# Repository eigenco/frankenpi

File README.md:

# frankenpi

This is an experimental project to connect Raspberry Pi with the help of cheap Cyclone IV FPGA board to 8-bit ISA bus to act as multiple different devices.

What is currently implemented (to some degree), i.e. PC can access through ISA
- Mass storage access from a file on the Raspberry Pi (written sectors are flushed every 2 seconds by default)
- Adlib output to optical SPDIF
- Sound Blaster 8-bit mono with DMA and IRQ (basic functions only), output to optical SPDIF
- Gravis Ultrasound (basic wavetable only), output to optical SPDIF
- Roland MT-32 (UART only), output to optical SPDIF
- USB mouse plugged into the Raspberry Pi will appear as a kind of serial mouse in DOS, custom ctmouse driver is provided (start with /v)
- Boot from custom TVGA9000i VGABIOS, i.e. no other devices are required to be present in the ISA bus besides FrakenPi and VGA-adapter

Youtube links:

https://www.youtube.com/watch?v=1ej76w8sHxY

https://www.youtube.com/watch?v=CkwgHHmKaSI

TESTED and working:
- Wolfenstein 3D (SB & Adlib)
- Second Reality (GUS)
- Scream Tracker 3.21 (SB1 and GUS)
- Skyroads (SB & Adlib)
- Keen 4 (Adlib)
- Monkey Island (Adlib/MT32/Mouse)
- Space Quest 3 (Adlib/Mouse)
- Space Quest 4 (Adlib/MT32/Mouse)
- Lotus 3 (Adlib)
- Lemmings (Adlib/Mouse)
- Eye of the Beholder I & II (Adlib/Mouse)
- Indiana Jones and the Fate of Atlantis (Adlib/MT32/Mouse)

Planned
- General MIDI
- MPU-401 support
- Sound Blaster AWE32 wavetable support
- Standard ATA at ports 1f0h-1f7h
- Compatibility improvements
- Boot ROM in the FPGA so hacked VGABIOS isn't required
- VGA output

Used resources
- Harddisk: ports 170h-171h
- SoundBlaster: ports 22ah-22eh corresponding ot base address of 220h, IRQ 7 and DMA 1
- MT32: 330h-331h
- Gravis Ultrasound: ports 341h-347h corresponding to base address of 240h
- Adlib: ports 388h-389h (standard)
- Mouse: port 3f8h and IRQ 4 (COM1)
- Bootcode for custom int 13h resides in hacked VGABIOS at the end of C0000-C7FFF memory region

Further explanation
- Outgoing port operations are transferred from the FPGA to the Raspberry Pi GPIO using dedicated unidirectional 8-bit data bus
- Incoming data from the Raspberry Pi GPIO (PCM, harddisk, mouse) is transferred using dedicated unidirectional 8-bit data bus
- Raspberry Pi: CPU0 handles hdd flushing and mouse, CPU1 handles GPIO transfers, CPU2 handles Adlib, Gravis Ultrasound and MT32 (software selected)
- Raspberry Pi operates with CPU1-CPU3 in isolated mode, all CPUs run at constant 1 GHz and sched_rt_runtime_us is -1
- Raspberry Pi generates sound data 64 samples at a time (16-bit stereo corresponds to 256 bytes it must transfer every 1.45ms or so)
- SPDIF is running in 24-bit 44100 Hz Stereo
- Hardcoded harddisk type is CHS 256/16/63, i.e. approx. 126MiB

Plan for the next PCB
- ICE40HX8K-CT256 (FPGA) seems to be available at Mouser
- IS61WV102416FBLL-10TLI (2 MByte SRAM) seem to be available at Mouser
- Created KiCAD project (PCB_v2)

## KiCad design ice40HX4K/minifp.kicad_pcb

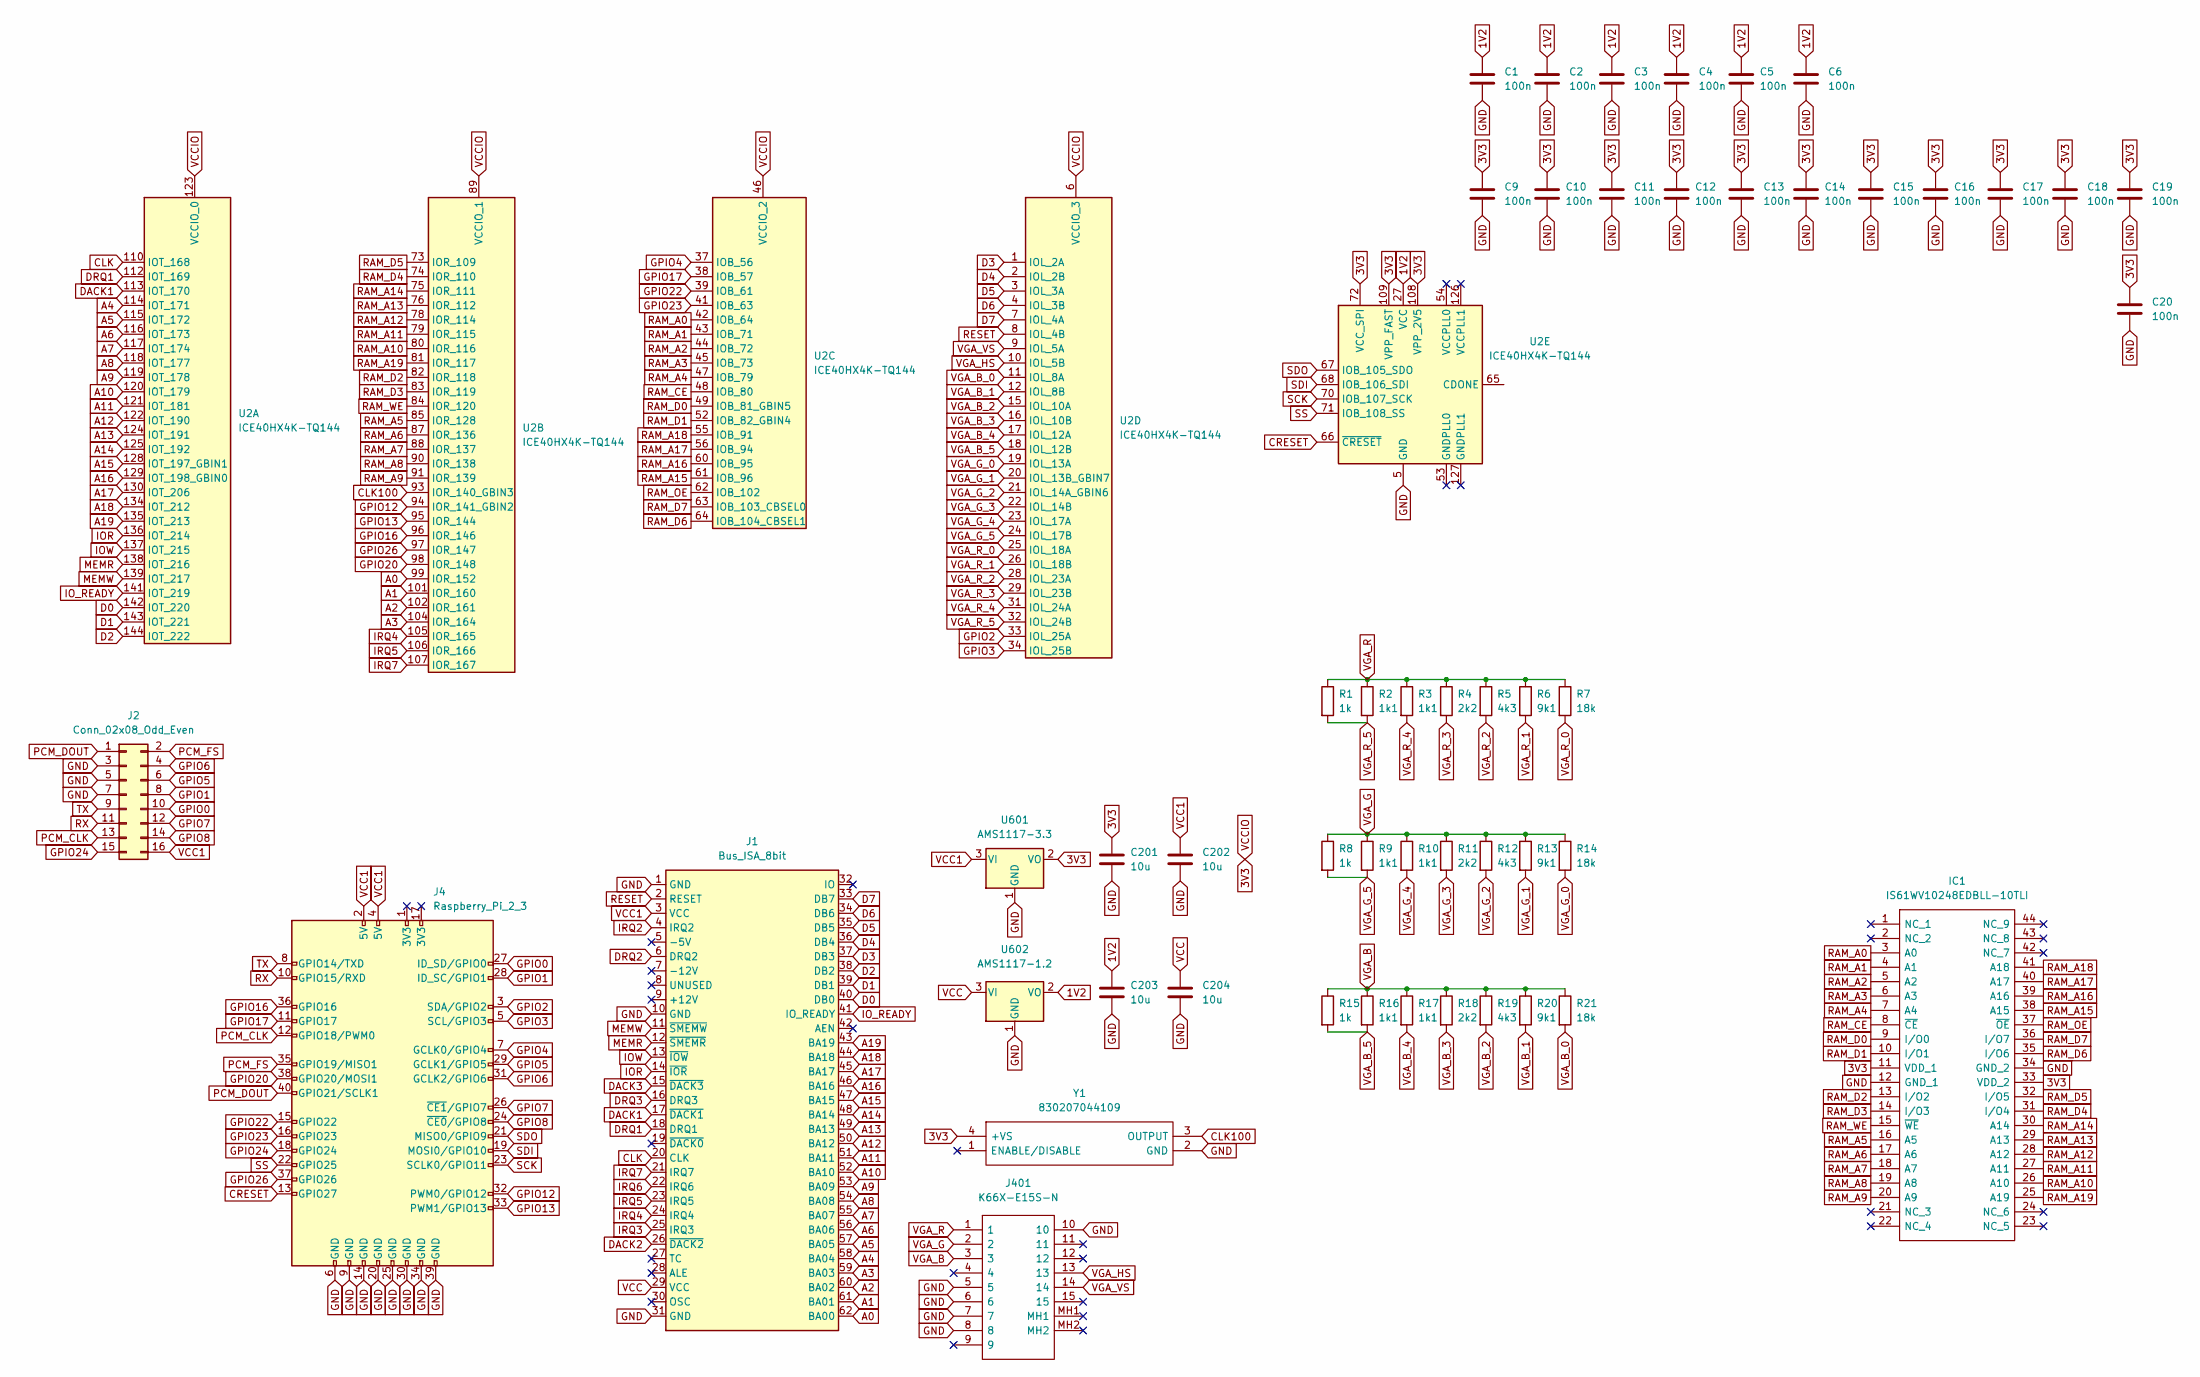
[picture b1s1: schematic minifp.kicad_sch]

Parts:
C1, C2, C3, C4, C5, C6, C9, C10, C11, C12, C13, C14, C15, C16, C17, C18, C19, C20: 100n; C_0603_1608Metric
C201, C202, C203, C204: 10u; C_0603_1608Metric
IC1: IS61WV10248EDBLL-10TLI; SOP80P1176X120-44N; Mouser Part Number 870-61WV10EDBLL10TLI
J1: Bus_ISA_8bit; Conn_Bus_ISA8
J2: Conn_02x08_Odd_Even; PinHeader_2x08_P1.27mm_Vertical
J4: Raspberry_Pi_2_3; PinHeader_2x20_P2.54mm_Vertical
J401: K66X-E15S-N; K66XE15SN; Mouser Part Number 806-K66X-E15S-N
R1, R8, R15: 1k; R_0603_1608Metric
R2, R3, R9, R10, R16, R17: 1k1; R_0603_1608Metric
R4, R11, R18: 2k2; R_0603_1608Metric
R5, R12, R19: 4k3; R_0603_1608Metric
R6, R13, R20: 9k1; R_0603_1608Metric
R7, R14, R21: 18k; R_0603_1608Metric
U2: ICE40HX4K-TQ144; TQFP-144_20x20mm_P0.5mm
U601: AMS1117-3.3; SOT-223-3_TabPin2
U602: AMS1117-1.2; SOT-223-3_TabPin2
Y1: 830207044109; Manufacturer_Part_Number 830207044109

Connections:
1V2: C1.1, C2.1, C3.1, C4.1, C5.1, C6.1, C203.1, U2.27 (VCC), U2.40 (VCC), U2.92 (VCC), U2.111 (VCC), U602.2 (VO)
3V3: C9.1, C10.1, C11.1, C12.1, C13.1, C14.1, C15.1, C16.1, C17.1, C18.1, C19.1, C20.1, C201.1, IC1.11 (VDD_1), IC1.33 (VDD_2), U2.6 (VCCIO_3), U2.30 (VCCIO_3), U2.46 (VCCIO_2), U2.57 (VCCIO_2), U2.72 (VCC_SPI), U2.89 (VCCIO_1), U2.100 (VCCIO_1), U2.108 (VPP_2V5), U2.109 (VPP_FAST), U2.123 (VCCIO_0), U2.131 (VCCIO_0), U601.2 (VO), Y1.4 (+VS)
A0: J1.62 (BA00), U2.99 (IOR_152)
A1: J1.61 (BA01), U2.101 (IOR_160)
A2: J1.60 (BA02), U2.102 (IOR_161)
A3: J1.59 (BA03), U2.104 (IOR_164)
A4: J1.58 (BA04), U2.114 (IOT_171)
A5: J1.57 (BA05), U2.115 (IOT_172)
A6: J1.56 (BA06), U2.116 (IOT_173)
A7: J1.55 (BA07), U2.117 (IOT_174)
A8: J1.54 (BA08), U2.118 (IOT_177)
A9: J1.53 (BA09), U2.119 (IOT_178)
A10: J1.52 (BA10), U2.120 (IOT_179)
A11: J1.51 (BA11), U2.121 (IOT_181)
A12: J1.50 (BA12), U2.122 (IOT_190)
A13: J1.49 (BA13), U2.124 (IOT_191)
A14: J1.48 (BA14), U2.125 (IOT_192)
A15: J1.47 (BA15), U2.128 (IOT_197_GBIN1)
A16: J1.46 (BA16), U2.129 (IOT_198_GBIN0)
A17: J1.45 (BA17), U2.130 (IOT_206)
A18: J1.44 (BA18), U2.134 (IOT_212)
A19: J1.43 (BA19), U2.135 (IOT_213)
CLK: J1.20 (CLK), U2.110 (IOT_168)
CLK100: U2.93 (IOR_140_GBIN3), Y1.3 (OUTPUT)
CRESET: J4.13 (GPIO27), U2.66 (~CRESET)
D0: J1.40 (DB0), U2.142 (IOT_220)
D1: J1.39 (DB1), U2.143 (IOT_221)
D2: J1.38 (DB2), U2.144 (IOT_222)
D3: J1.37 (DB3), U2.1 (IOL_2A)
D4: J1.36 (DB4), U2.2 (IOL_2B)
D5: J1.35 (DB5), U2.3 (IOL_3A)
D6: J1.34 (DB6), U2.4 (IOL_3B)
D7: J1.33 (DB7), U2.7 (IOL_4A)
DACK1: J1.17 (~DACK1), U2.113 (IOT_170)
DACK2: J1.26 (~DACK2)
DACK3: J1.15 (~DACK3)
DRQ1: J1.18 (DRQ1), U2.112 (IOT_169)
DRQ2: J1.6 (DRQ2)
DRQ3: J1.16 (DRQ3)
GND: C1.2, C2.2, C3.2, C4.2, C5.2, C6.2, C9.2, C10.2, C11.2, C12.2, C13.2, C14.2, C15.2, C16.2, C17.2, C18.2, C19.2, C20.2, C201.2, C202.2, C203.2, C204.2, IC1.12 (GND_1), IC1.34 (GND_2), J1.1 (GND), J1.10 (GND), J1.31 (GND), J2.3, J2.5, J2.7, J4.6 (GND), J4.9 (GND), J4.14 (GND), J4.20 (GND), J4.25 (GND), J4.30 (GND), J4.34 (GND), J4.39 (GND), J401.5, J401.6, J401.7, J401.8, J401.10, U2.5 (GND), U2.13 (GND), U2.14 (GND), U2.59 (GND), U2.69 (GND), U2.86 (GND), U2.103 (GND), U2.132 (GND), U2.140 (GND), U601.1 (GND), U602.1 (GND), Y1.2 (GND)
GPIO0: J2.10, J4.27 (ID_SD/GPIO0)
GPIO1: J2.8, J4.28 (ID_SC/GPIO1)
GPIO2: J4.3 (SDA/GPIO2), U2.33 (IOL_25A)
GPIO3: J4.5 (SCL/GPIO3), U2.34 (IOL_25B)
GPIO4: J4.7 (GCLK0/GPIO4), U2.37 (IOB_56)
GPIO5: J2.6, J4.29 (GCLK1/GPIO5)
GPIO6: J2.4, J4.31 (GCLK2/GPIO6)
GPIO7: J2.12, J4.26 (~CE1/GPIO7)
GPIO8: J2.14, J4.24 (~CE0/GPIO8)
GPIO12: J4.32 (PWM0/GPIO12), U2.94 (IOR_141_GBIN2)
GPIO13: J4.33 (PWM1/GPIO13), U2.95 (IOR_144)
GPIO16: J4.36 (GPIO16), U2.96 (IOR_146)
GPIO17: J4.11 (GPIO17), U2.38 (IOB_57)
GPIO20: J4.38 (GPIO20/MOSI1), U2.98 (IOR_148)
GPIO22: J4.15 (GPIO22), U2.39 (IOB_61)
GPIO23: J4.16 (GPIO23), U2.41 (IOB_63)
GPIO24: J2.15, J4.18 (GPIO24)
GPIO26: J4.37 (GPIO26), U2.97 (IOR_147)
IOR: J1.14 (~IOR), U2.136 (IOT_214)
IOW: J1.13 (~IOW), U2.137 (IOT_215)
IO_READY: J1.41 (IO_READY), U2.141 (IOT_219)
IRQ2: J1.4 (IRQ2)
IRQ3: J1.25 (IRQ3)
IRQ4: J1.24 (IRQ4), U2.105 (IOR_165)
IRQ5: J1.23 (IRQ5), U2.106 (IOR_166)
IRQ6: J1.22 (IRQ6)
IRQ7: J1.21 (IRQ7), U2.107 (IOR_167)
MEMR: J1.12 (~SMEMR), U2.138 (IOT_216)
MEMW: J1.11 (~SMEMW), U2.139 (IOT_217)
PCM_CLK: J2.13, J4.12 (GPIO18/PWM0)
PCM_DOUT: J2.1, J4.40 (GPIO21/SCLK1)
PCM_FS: J2.2, J4.35 (GPIO19/MISO1)
RAM_A0: IC1.3 (A0), U2.42 (IOB_64)
RAM_A1: IC1.4 (A1), U2.43 (IOB_71)
RAM_A2: IC1.5 (A2), U2.44 (IOB_72)
RAM_A3: IC1.6 (A3), U2.45 (IOB_73)
RAM_A4: IC1.7 (A4), U2.47 (IOB_79)
RAM_A5: IC1.16 (A5), U2.85 (IOR_128)
RAM_A6: IC1.17 (A6), U2.87 (IOR_136)
RAM_A7: IC1.18 (A7), U2.88 (IOR_137)
RAM_A8: IC1.19 (A8), U2.90 (IOR_138)
RAM_A9: IC1.20 (A9), U2.91 (IOR_139)
RAM_A10: IC1.26 (A10), U2.80 (IOR_116)
RAM_A11: IC1.27 (A11), U2.79 (IOR_115)
RAM_A12: IC1.28 (A12), U2.78 (IOR_114)
RAM_A13: IC1.29 (A13), U2.76 (IOR_112)
RAM_A14: IC1.30 (A14), U2.75 (IOR_111)
RAM_A15: IC1.38 (A15), U2.61 (IOB_96)
RAM_A16: IC1.39 (A16), U2.60 (IOB_95)
RAM_A17: IC1.40 (A17), U2.56 (IOB_94)
RAM_A18: IC1.41 (A18), U2.55 (IOB_91)
RAM_A19: IC1.25 (A19), U2.81 (IOR_117)
RAM_CE: IC1.8 (~CE), U2.48 (IOB_80)
RAM_D0: IC1.9 (I/O0), U2.49 (IOB_81_GBIN5)
RAM_D1: IC1.10 (I/O1), U2.52 (IOB_82_GBIN4)
RAM_D2: IC1.13 (I/O2), U2.82 (IOR_118)
RAM_D3: IC1.14 (I/O3), U2.83 (IOR_119)
RAM_D4: IC1.31 (I/O4), U2.74 (IOR_110)
RAM_D5: IC1.32 (I/O5), U2.73 (IOR_109)
RAM_D6: IC1.35 (I/O6), U2.64 (IOB_104_CBSEL1)
RAM_D7: IC1.36 (I/O7), U2.63 (IOB_103_CBSEL0)
RAM_OE: IC1.37 (~OE), U2.62 (IOB_102)
RAM_WE: IC1.15 (~WE), U2.84 (IOR_120)
RESET: J1.2 (RESET), U2.8 (IOL_4B)
RX: J2.11, J4.10 (GPIO15/RXD)
SCK: J4.23 (SCLK0/GPIO11), U2.70 (IOB_107_SCK)
SDI: J4.19 (MOSI0/GPIO10), U2.68 (IOB_106_SDI)
SDO: J4.21 (MISO0/GPIO9), U2.67 (IOB_105_SDO)
SS: J4.22 (GPIO25), U2.71 (IOB_108_SS)
TX: J2.9, J4.8 (GPIO14/TXD)
VCC: C204.1, J1.29 (VCC), U602.3 (VI)
VCC1: C202.1, J1.3 (VCC), J2.16, J4.2 (5V), J4.4 (5V), U601.3 (VI)
VGA_B: J401.3, R15.1, R16.1, R17.1, R18.1, R19.1, R20.1, R21.1
VGA_B_0: R21.2, U2.11 (IOL_8A)
VGA_B_1: R20.2, U2.12 (IOL_8B)
VGA_B_2: R19.2, U2.15 (IOL_10A)
VGA_B_3: R18.2, U2.16 (IOL_10B)
VGA_B_4: R17.2, U2.17 (IOL_12A)
VGA_B_5: R15.2, R16.2, U2.18 (IOL_12B)
VGA_G: J401.2, R8.1, R9.1, R10.1, R11.1, R12.1, R13.1, R14.1
VGA_G_0: R14.2, U2.19 (IOL_13A)
VGA_G_1: R13.2, U2.20 (IOL_13B_GBIN7)
VGA_G_2: R12.2, U2.21 (IOL_14A_GBIN6)
VGA_G_3: R11.2, U2.22 (IOL_14B)
VGA_G_4: R10.2, U2.23 (IOL_17A)
VGA_G_5: R8.2, R9.2, U2.24 (IOL_17B)
VGA_HS: J401.13, U2.10 (IOL_5B)
VGA_R: J401.1, R1.1, R2.1, R3.1, R4.1, R5.1, R6.1, R7.1
VGA_R_0: R7.2, U2.25 (IOL_18A)
VGA_R_1: R6.2, U2.26 (IOL_18B)
VGA_R_2: R5.2, U2.28 (IOL_23A)
VGA_R_3: R4.2, U2.29 (IOL_23B)
VGA_R_4: R3.2, U2.31 (IOL_24A)
VGA_R_5: R1.2, R2.2, U2.32 (IOL_24B)
VGA_VS: J401.14, U2.9 (IOL_5A)

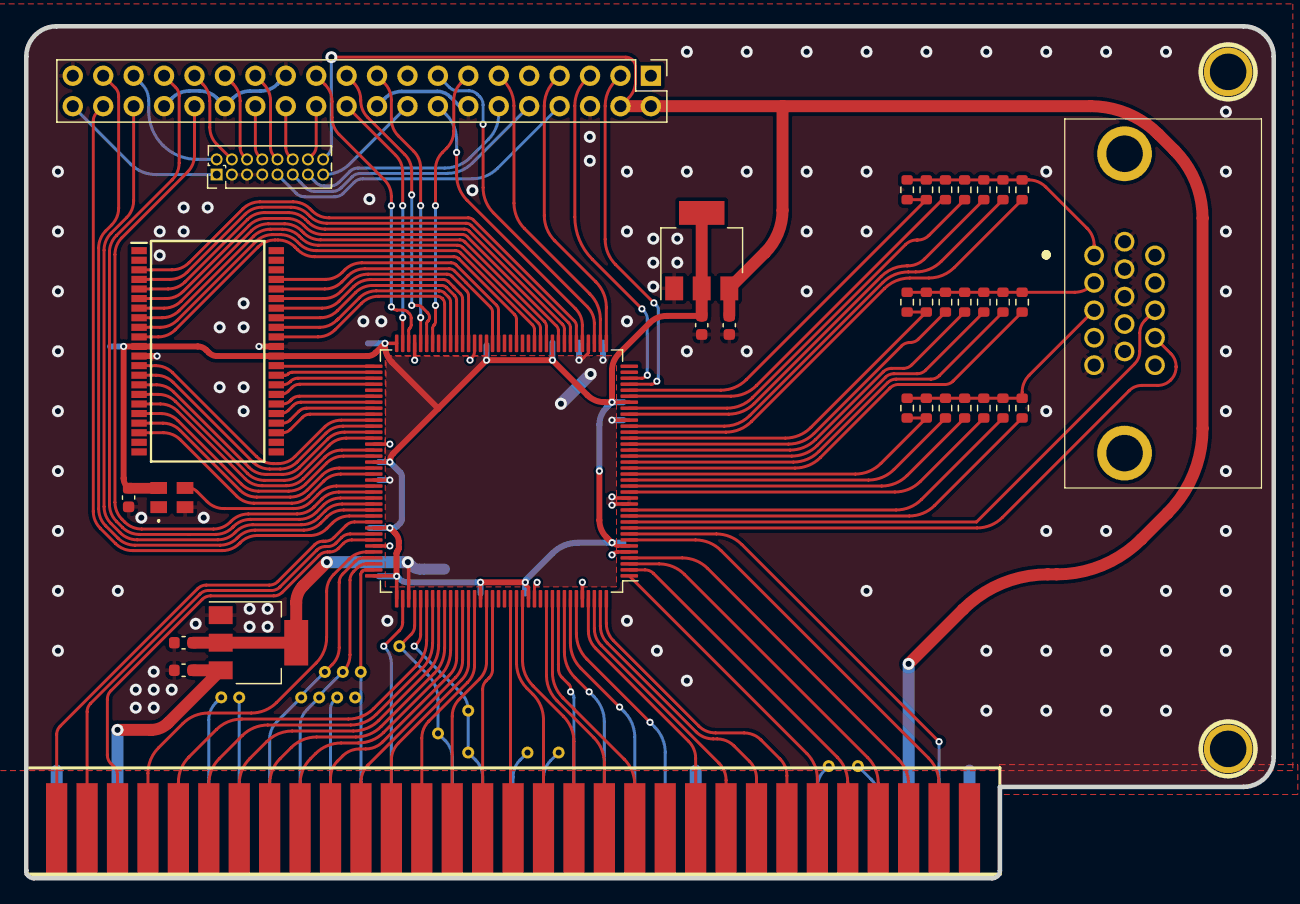
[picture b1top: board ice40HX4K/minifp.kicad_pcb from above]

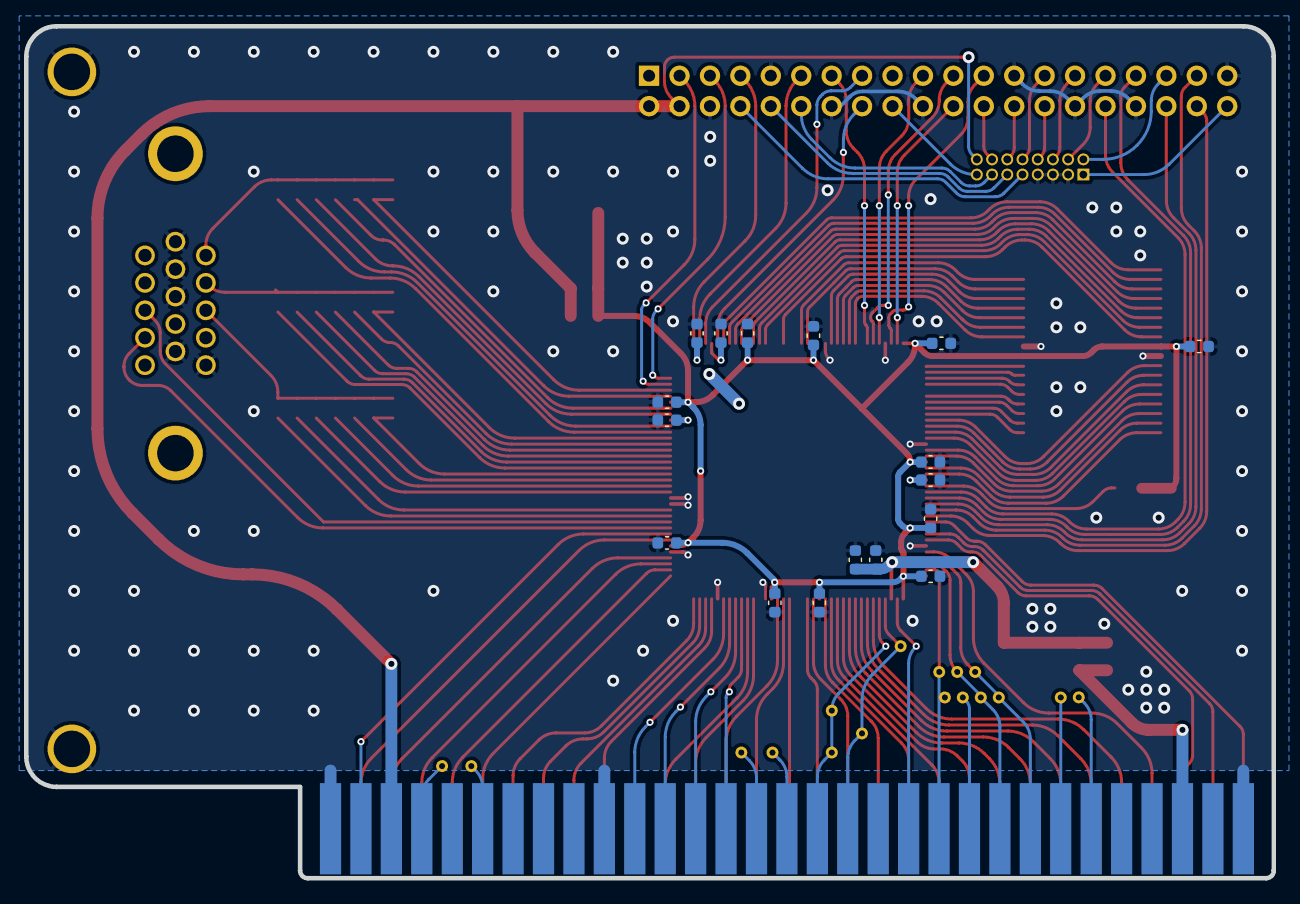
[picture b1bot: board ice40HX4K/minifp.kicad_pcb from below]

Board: 2 copper layers, 104.1 x 71.1 mm, 52 parts (17 on the bottom side), 128 nets.

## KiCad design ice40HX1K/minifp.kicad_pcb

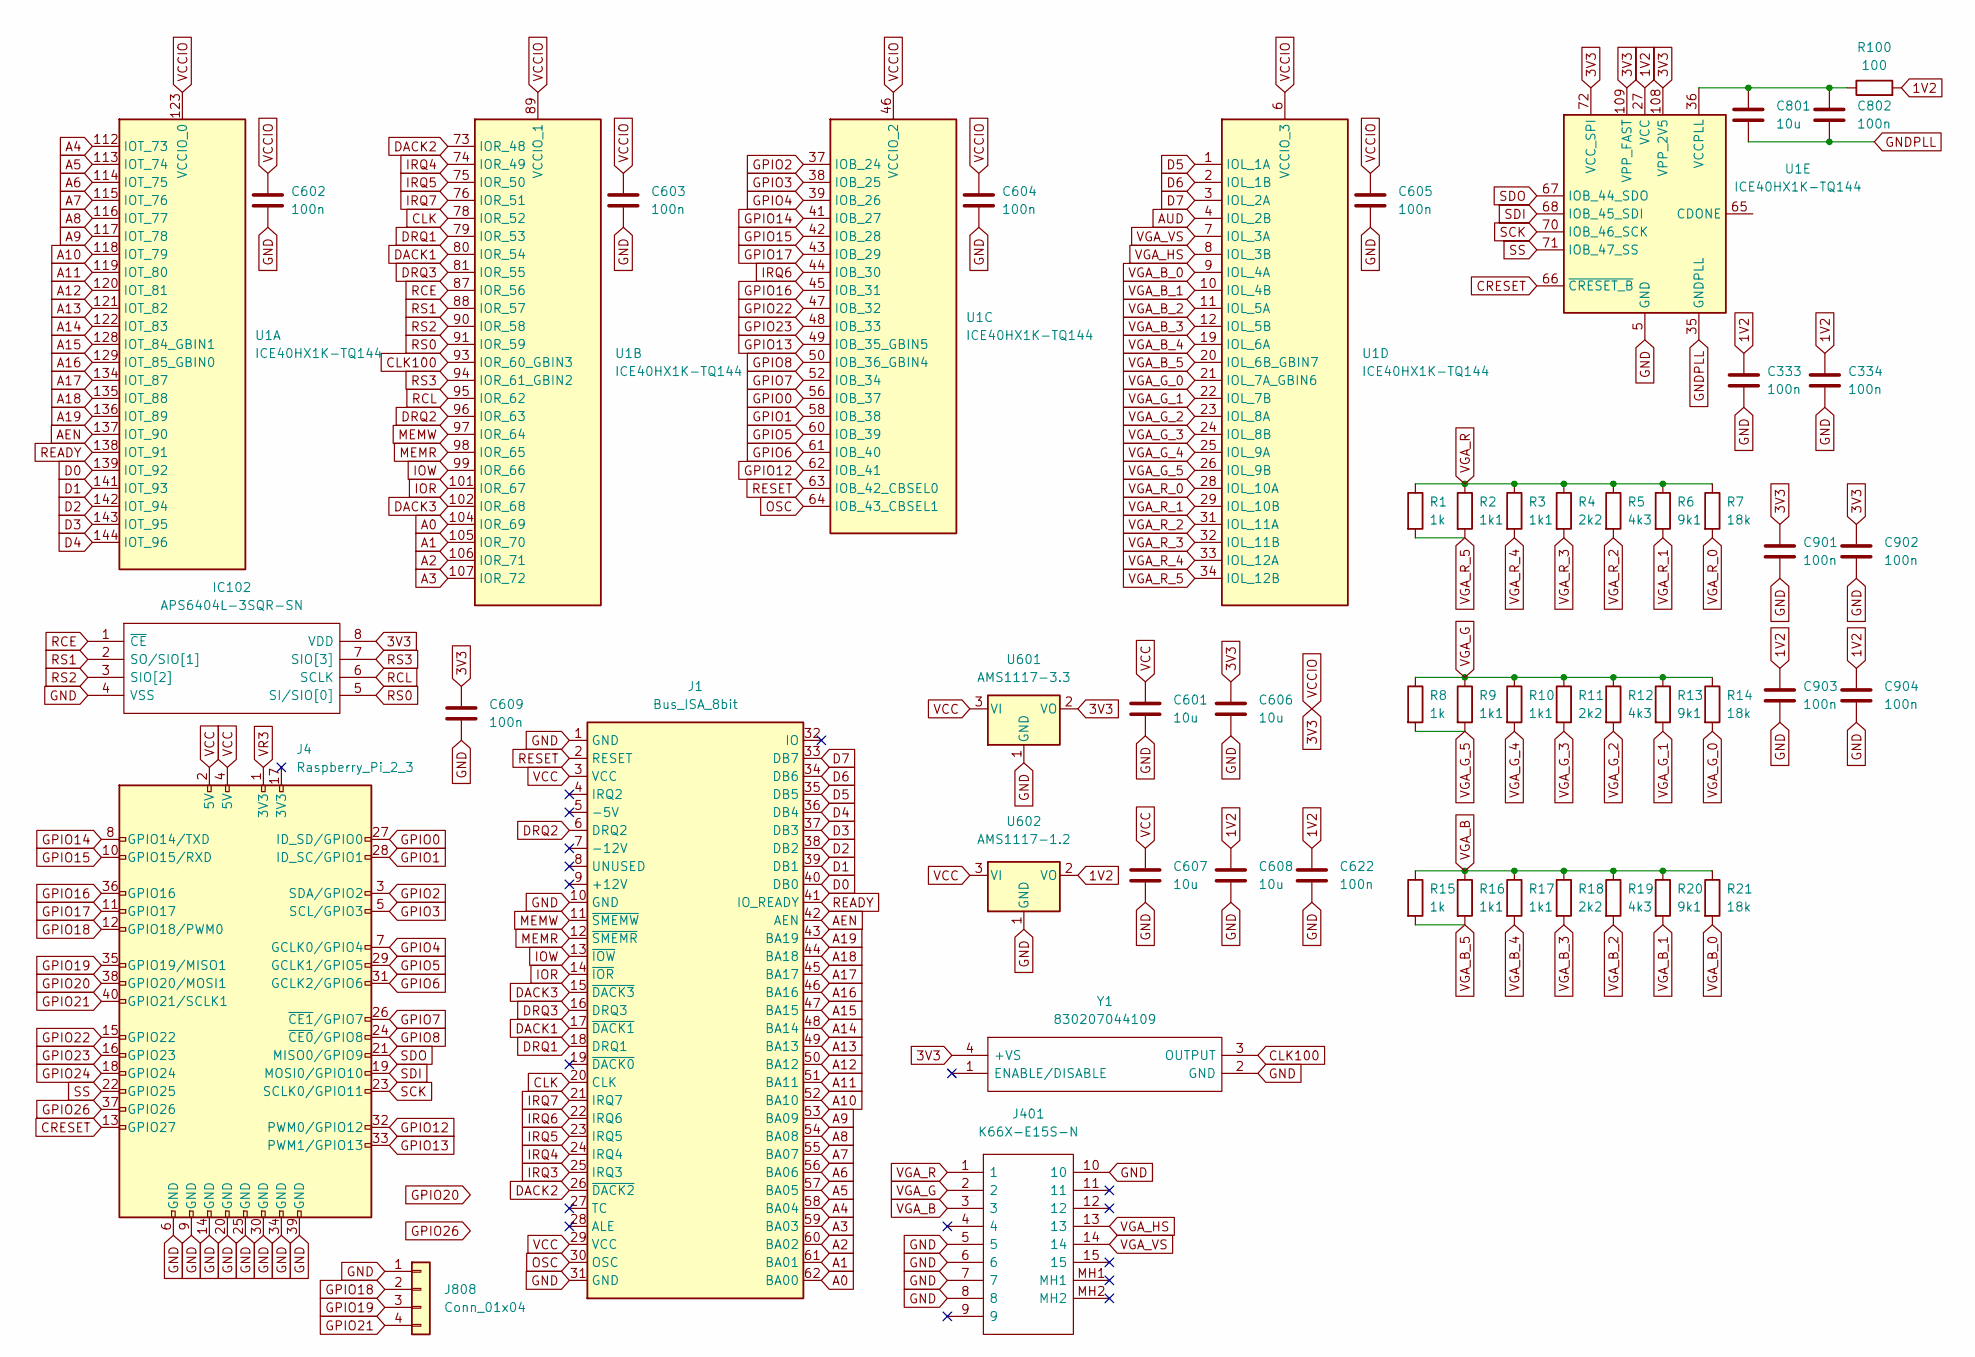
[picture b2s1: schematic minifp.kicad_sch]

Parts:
C333, C334, C602, C603, C604, C605, C609, C622, C802, C901, C902, C903, C904: 100n; C_0603_1608Metric
C601, C606, C607, C608, C801: 10u; C_0603_1608Metric
IC102: APS6404L-3SQR-SN; SOIC127P600X175-8N; Mouser Part Number 878-APS6404L-3SQR-SN
J1: Bus_ISA_8bit; Conn_Bus_ISA8
J4: Raspberry_Pi_2_3; PinHeader_2x20_P2.54mm_Vertical
J401: K66X-E15S-N; K66XE15SN; Mouser Part Number 806-K66X-E15S-N
J808: Conn_01x04; PinHeader_1x04_P2.54mm_Vertical
R1, R8, R15: 1k; R_0603_1608Metric
R2, R3, R9, R10, R16, R17: 1k1; R_0603_1608Metric
R4, R11, R18: 2k2; R_0603_1608Metric
R5, R12, R19: 4k3; R_0603_1608Metric
R6, R13, R20: 9k1; R_0603_1608Metric
R7, R14, R21: 18k; R_0603_1608Metric
R100: 100; R_0603_1608Metric
U1: ICE40HX1K-TQ144; TQFP-144_20x20mm_P0.5mm
U601: AMS1117-3.3; SOT-223-3_TabPin2
U602: AMS1117-1.2; SOT-223-3_TabPin2
Y1: 830207044109; Manufacturer_Part_Number 830207044109

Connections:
1V2: C333.1, C334.1, C608.1, C622.1, C903.1, C904.1, R100.2, U1.27 (VCC), U1.51 (VCC), U1.92 (VCC), U1.111 (VCC), U602.2 (VO)
3V3: C602.1, C603.1, C604.1, C605.1, C606.1, C609.1, C901.1, C902.1, IC102.8 (VDD), U1.6 (VCCIO_3), U1.30 (VCCIO_3), U1.46 (VCCIO_2), U1.57 (VCCIO_2), U1.72 (VCC_SPI), U1.89 (VCCIO_1), U1.100 (VCCIO_1), U1.108 (VPP_2V5), U1.109 (VPP_FAST), U1.123 (VCCIO_0), U1.133 (VCCIO_0), U601.2 (VO), Y1.4 (+VS)
A0: J1.62 (BA00), U1.104 (IOR_69)
A1: J1.61 (BA01), U1.105 (IOR_70)
A2: J1.60 (BA02), U1.106 (IOR_71)
A3: J1.59 (BA03), U1.107 (IOR_72)
A4: J1.58 (BA04), U1.112 (IOT_73)
A5: J1.57 (BA05), U1.113 (IOT_74)
A6: J1.56 (BA06), U1.114 (IOT_75)
A7: J1.55 (BA07), U1.115 (IOT_76)
A8: J1.54 (BA08), U1.116 (IOT_77)
A9: J1.53 (BA09), U1.117 (IOT_78)
A10: J1.52 (BA10), U1.118 (IOT_79)
A11: J1.51 (BA11), U1.119 (IOT_80)
A12: J1.50 (BA12), U1.120 (IOT_81)
A13: J1.49 (BA13), U1.121 (IOT_82)
A14: J1.48 (BA14), U1.122 (IOT_83)
A15: J1.47 (BA15), U1.128 (IOT_84_GBIN1)
A16: J1.46 (BA16), U1.129 (IOT_85_GBIN0)
A17: J1.45 (BA17), U1.134 (IOT_87)
A18: J1.44 (BA18), U1.135 (IOT_88)
A19: J1.43 (BA19), U1.136 (IOT_89)
AEN: J1.42 (AEN), U1.137 (IOT_90)
AUD: U1.4 (IOL_2B)
CLK: J1.20 (CLK), U1.78 (IOR_52)
CLK100: U1.93 (IOR_60_GBIN3), Y1.3 (OUTPUT)
CRESET: J4.13 (GPIO27), U1.66 (~CRESET_B)
D0: J1.40 (DB0), U1.139 (IOT_92)
D1: J1.39 (DB1), U1.141 (IOT_93)
D2: J1.38 (DB2), U1.142 (IOT_94)
D3: J1.37 (DB3), U1.143 (IOT_95)
D4: J1.36 (DB4), U1.144 (IOT_96)
D5: J1.35 (DB5), U1.1 (IOL_1A)
D6: J1.34 (DB6), U1.2 (IOL_1B)
D7: J1.33 (DB7), U1.3 (IOL_2A)
DACK1: J1.17 (~DACK1), U1.80 (IOR_54)
DACK2: J1.26 (~DACK2), U1.73 (IOR_48)
DACK3: J1.15 (~DACK3), U1.102 (IOR_68)
DRQ1: J1.18 (DRQ1), U1.79 (IOR_53)
DRQ2: J1.6 (DRQ2), U1.96 (IOR_63)
DRQ3: J1.16 (DRQ3), U1.81 (IOR_55)
GND: C333.2, C334.2, C601.2, C602.2, C603.2, C604.2, C605.2, C606.2, C607.2, C608.2, C609.2, C622.2, C901.2, C902.2, C903.2, C904.2, IC102.4 (VSS), J1.1 (GND), J1.10 (GND), J1.31 (GND), J4.6 (GND), J4.9 (GND), J4.14 (GND), J4.20 (GND), J4.25 (GND), J4.30 (GND), J4.34 (GND), J4.39 (GND), J401.5, J401.6, J401.7, J401.8, J401.10, J808.1, U1.5 (GND), U1.13 (GND), U1.14 (GND), U1.59 (GND), U1.69 (GND), U1.86 (GND), U1.103 (GND), U1.132 (GND), U1.140 (GND), U601.1 (GND), U602.1 (GND), Y1.2 (GND)
GNDPLL: C801.2, C802.2, U1.35 (GNDPLL)
GPIO0: J4.27 (ID_SD/GPIO0), U1.56 (IOB_37)
GPIO1: J4.28 (ID_SC/GPIO1), U1.58 (IOB_38)
GPIO2: J4.3 (SDA/GPIO2), U1.37 (IOB_24)
GPIO3: J4.5 (SCL/GPIO3), U1.38 (IOB_25)
GPIO4: J4.7 (GCLK0/GPIO4), U1.39 (IOB_26)
GPIO5: J4.29 (GCLK1/GPIO5), U1.60 (IOB_39)
GPIO6: J4.31 (GCLK2/GPIO6), U1.61 (IOB_40)
GPIO7: J4.26 (~CE1/GPIO7), U1.52 (IOB_34)
GPIO8: J4.24 (~CE0/GPIO8), U1.50 (IOB_36_GBIN4)
GPIO12: J4.32 (PWM0/GPIO12), U1.62 (IOB_41)
GPIO13: J4.33 (PWM1/GPIO13), U1.49 (IOB_35_GBIN5)
GPIO14: J4.8 (GPIO14/TXD), U1.41 (IOB_27)
GPIO15: J4.10 (GPIO15/RXD), U1.42 (IOB_28)
GPIO16: J4.36 (GPIO16), U1.45 (IOB_31)
GPIO17: J4.11 (GPIO17), U1.43 (IOB_29)
GPIO18: J4.12 (GPIO18/PWM0), J808.2
GPIO19: J4.35 (GPIO19/MISO1), J808.3
GPIO20: J4.38 (GPIO20/MOSI1)
GPIO21: J4.40 (GPIO21/SCLK1), J808.4
GPIO22: J4.15 (GPIO22), U1.47 (IOB_32)
GPIO23: J4.16 (GPIO23), U1.48 (IOB_33)
GPIO24: J4.18 (GPIO24)
GPIO26: J4.37 (GPIO26)
IOR: J1.14 (~IOR), U1.101 (IOR_67)
IOW: J1.13 (~IOW), U1.99 (IOR_66)
IRQ3: J1.25 (IRQ3)
IRQ4: J1.24 (IRQ4), U1.74 (IOR_49)
IRQ5: J1.23 (IRQ5), U1.75 (IOR_50)
IRQ6: J1.22 (IRQ6), U1.44 (IOB_30)
IRQ7: J1.21 (IRQ7), U1.76 (IOR_51)
MEMR: J1.12 (~SMEMR), U1.98 (IOR_65)
MEMW: J1.11 (~SMEMW), U1.97 (IOR_64)
unnamed: C801.1, C802.1, R100.1, U1.36 (VCCPLL)
OSC: J1.30 (OSC), U1.64 (IOB_43_CBSEL1)
RCE: IC102.1 (~CE), U1.87 (IOR_56)
RCL: IC102.6 (SCLK), U1.95 (IOR_62)
READY: J1.41 (IO_READY), U1.138 (IOT_91)
RESET: J1.2 (RESET), U1.63 (IOB_42_CBSEL0)
RS0: IC102.5 (SI/SIO[0]), U1.91 (IOR_59)
RS1: IC102.2 (SO/SIO[1]), U1.88 (IOR_57)
RS2: IC102.3 (SIO[2]), U1.90 (IOR_58)
RS3: IC102.7 (SIO[3]), U1.94 (IOR_61_GBIN2)
SCK: J4.23 (SCLK0/GPIO11), U1.70 (IOB_46_SCK)
SDI: J4.19 (MOSI0/GPIO10), U1.68 (IOB_45_SDI)
SDO: J4.21 (MISO0/GPIO9), U1.67 (IOB_44_SDO)
SS: J4.22 (GPIO25), U1.71 (IOB_47_SS)
VCC: C601.1, C607.1, J1.3 (VCC), J1.29 (VCC), J4.2 (5V), J4.4 (5V), U601.3 (VI), U602.3 (VI)
VGA_B: J401.3, R15.1, R16.1, R17.1, R18.1, R19.1, R20.1, R21.1
VGA_B_0: R21.2, U1.9 (IOL_4A)
VGA_B_1: R20.2, U1.10 (IOL_4B)
VGA_B_2: R19.2, U1.11 (IOL_5A)
VGA_B_3: R18.2, U1.12 (IOL_5B)
VGA_B_4: R17.2, U1.19 (IOL_6A)
VGA_B_5: R15.2, R16.2, U1.20 (IOL_6B_GBIN7)
VGA_G: J401.2, R8.1, R9.1, R10.1, R11.1, R12.1, R13.1, R14.1
VGA_G_0: R14.2, U1.21 (IOL_7A_GBIN6)
VGA_G_1: R13.2, U1.22 (IOL_7B)
VGA_G_2: R12.2, U1.23 (IOL_8A)
VGA_G_3: R11.2, U1.24 (IOL_8B)
VGA_G_4: R10.2, U1.25 (IOL_9A)
VGA_G_5: R8.2, R9.2, U1.26 (IOL_9B)
VGA_HS: J401.13, U1.8 (IOL_3B)
VGA_R: J401.1, R1.1, R2.1, R3.1, R4.1, R5.1, R6.1, R7.1
VGA_R_0: R7.2, U1.28 (IOL_10A)
VGA_R_1: R6.2, U1.29 (IOL_10B)
VGA_R_2: R5.2, U1.31 (IOL_11A)
VGA_R_3: R4.2, U1.32 (IOL_11B)
VGA_R_4: R3.2, U1.33 (IOL_12A)
VGA_R_5: R1.2, R2.2, U1.34 (IOL_12B)
VGA_VS: J401.14, U1.7 (IOL_3A)
VR3: J4.1 (3V3)

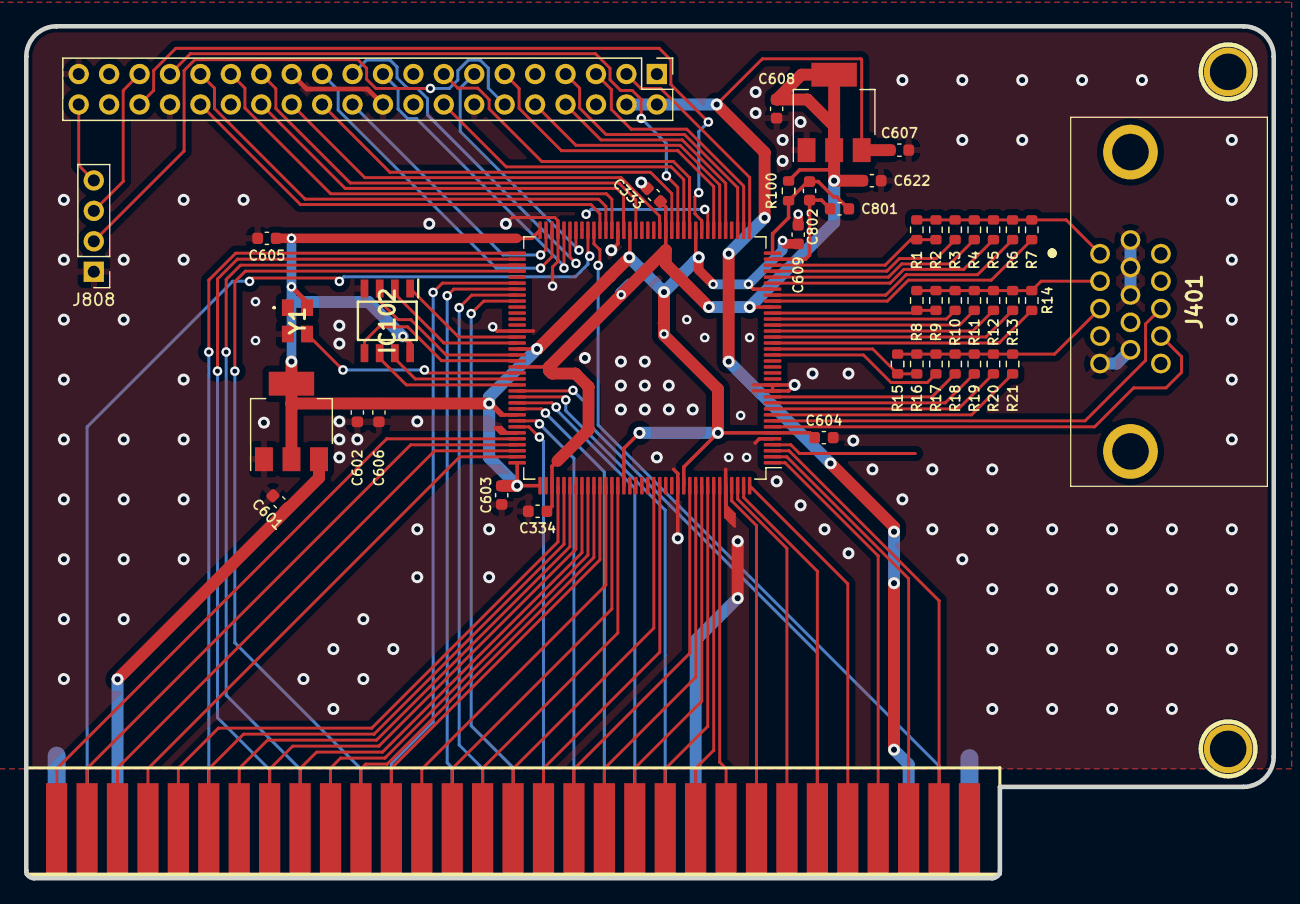
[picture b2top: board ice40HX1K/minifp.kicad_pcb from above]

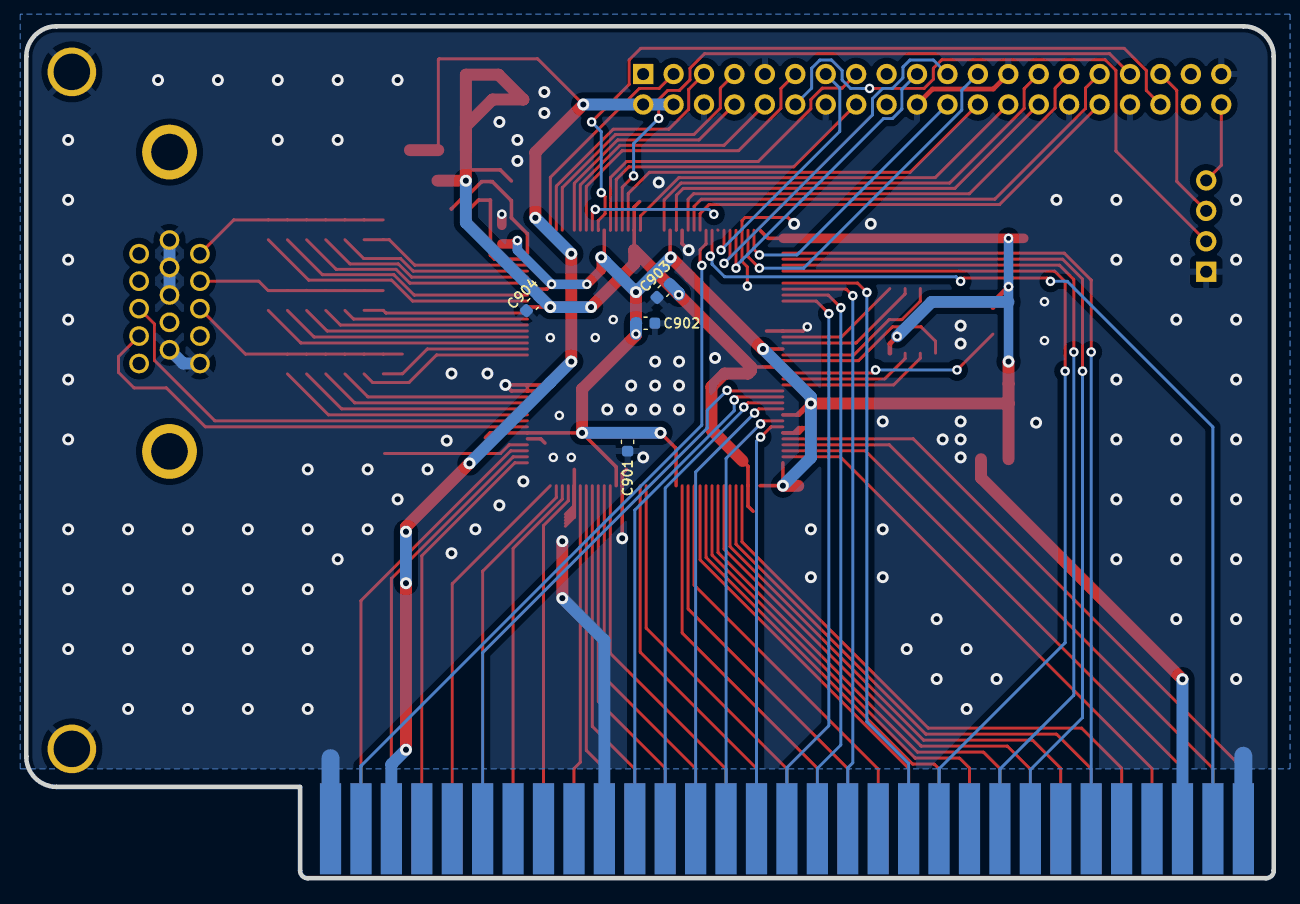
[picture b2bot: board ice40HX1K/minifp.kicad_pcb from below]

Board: 2 copper layers, 104.1 x 71.1 mm, 49 parts (4 on the bottom side), 108 nets.

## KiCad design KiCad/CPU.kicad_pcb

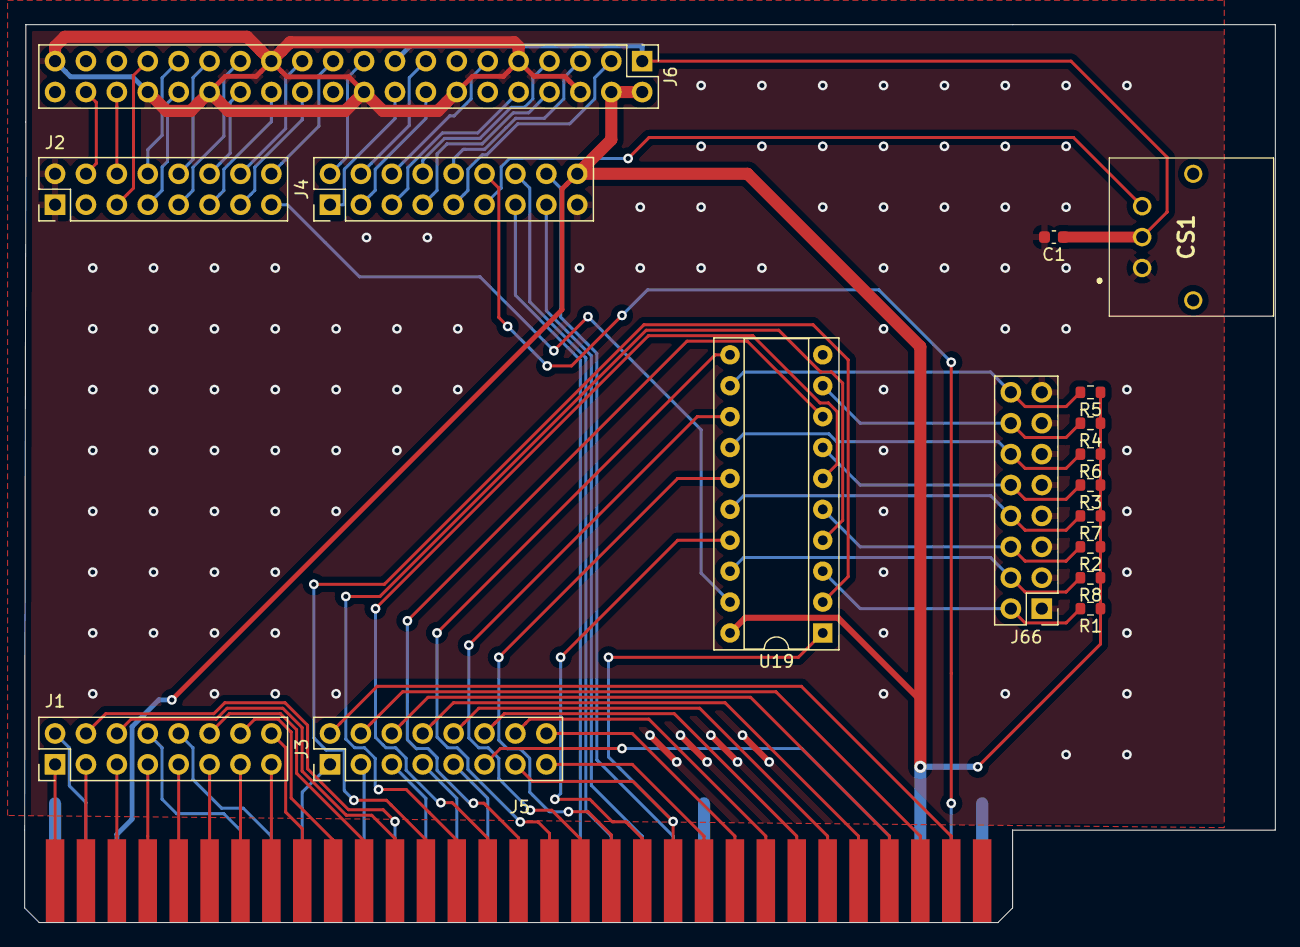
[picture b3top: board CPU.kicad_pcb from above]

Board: 2 copper layers, 102.8 x 73.8 mm, 18 parts (0 on the bottom side), 80 nets.

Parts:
C1: 0.1u; C_0603_1608Metric
CS1: TOTX1350_F_; TOTX1350F
J1, J2, J3, J66: Conn_02x08_Odd_Even; PinHeader_2x08_P2.54mm_Vertical
J4: Conn_02x09_Odd_Even; PinHeader_2x09_P2.54mm_Vertical
J5: Bus_ISA_8bit; BUS_PC
J6: Raspberry_Pi_2_3; PinHeader_2x20_P2.54mm_Vertical
R1, R2, R3, R4, R5, R6, R7, R8: 10k; R_0603_1608Metric
U19: 74LS688; DIP-20_W7.62mm_Socket

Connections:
A0: J1.1, J5.62 (BA00)
A1: J1.3, J5.61 (BA01)
A2: J1.5, J5.60 (BA02)
A3: J1.7, J5.59 (BA03)
A4: J1.9, J5.58 (BA04)
A5: J1.11, J5.57 (BA05)
A6: J1.13, J5.56 (BA06)
A7: J1.15, J5.55 (BA07)
A8: J1.16, J5.54 (BA08)
A9: J1.14, J5.53 (BA09)
A10: J1.12, J5.52 (BA10)
A11: J1.6, J5.51 (BA11)
A12: J5.50 (BA12), U19.2 (P0)
A13: J5.49 (BA13), U19.4 (P1)
A14: J5.48 (BA14), U19.6 (P2)
A15: J5.47 (BA15), U19.8 (P3)
A16: J5.46 (BA16), U19.11 (P4)
A17: J5.45 (BA17), U19.13 (P5)
A18: J5.44 (BA18), U19.15 (P6)
A19: J5.43 (BA19), U19.17 (P7)
AEN: J3.13, J5.42 (AEN), U19.1 (G)
CLK: J1.4, J5.20 (CLK)
D0: J3.16, J5.40 (DB0)
D1: J3.14, J5.39 (DB1)
D2: J3.12, J5.38 (DB2)
D3: J3.10, J5.37 (DB3)
D4: J3.8, J5.36 (DB4)
D5: J3.6, J5.35 (DB5)
D6: J3.4, J5.34 (DB6)
D7: J3.2, J5.33 (DB7)
DRQ1: J3.7, J5.18 (DRQ1)
GND: C1.2, CS1.1 (NC_1), J2.1, J2.2, J4.17, J5.1 (GND), J5.10 (GND), J5.31 (GND), J6.6 (GND), J6.9 (GND), J6.14 (GND), J6.20 (GND), J6.25 (GND), J6.30 (GND), J6.34 (GND), J6.39 (GND), J66.1, J66.3, J66.5, J66.7, J66.9, J66.11, J66.13, J66.15, U19.10 (GND)
IO_READY: J3.15, J5.41 (IO_READY)
IRQ1: J3.5, J5.19 (~DACK0)
IRQ2: J3.11, J5.4 (IRQ2)
IRQ3: J1.8, J5.25 (IRQ3)
IRQ4: J1.10, J5.24 (IRQ4)
IRQ5: J3.1, J5.23 (IRQ5)
IRQ7: J3.3, J5.21 (IRQ7)
OSC: J1.2, J5.30 (OSC)
R0: J66.2, R1.2, U19.3 (R0)
R1: J66.6, R2.2, U19.5 (R1)
R2: J66.10, R3.2, U19.7 (R2)
R3: J66.14, R4.2, U19.9 (R3)
R4: J66.16, R5.2, U19.12 (R4)
R5: J66.12, R6.2, U19.14 (R5)
R6: J66.8, R7.2, U19.16 (R6)
R7: J66.4, R8.2, U19.18 (R7)
RESET: J4.12, J5.2 (RESET)
ROM: J2.15, U19.19 (P=R)
RP0: J2.9, J6.27 (ID_SD/GPIO0)
RP1: J2.12, J6.28 (ID_SC/GPIO1)
RP2: J4.9, J6.3 (SDA/GPIO2)
RP3: J4.10, J6.5 (SCL/GPIO3)
RP4: J4.8, J6.7 (GCLK0/GPIO4)
RP5: J2.10, J6.29 (GCLK1/GPIO5)
RP6: J2.8, J6.31 (GCLK2/GPIO6)
RP7: J2.11, J6.26 (~CE1/GPIO7)
RP8: J2.13, J6.24 (~CE0/GPIO8)
RP9: J2.16, J6.21 (MISO0/GPIO9)
RP10: J4.2, J6.19 (MOSI0/GPIO10)
RP11: J2.14, J6.23 (SCLK0/GPIO11)
RP12: J2.7, J6.32 (PWM0/GPIO12)
RP13: J2.5, J6.33 (PWM1/GPIO13)
RP14: J4.7, J6.8 (GPIO14/TXD)
RP15: J4.5, J6.10 (GPIO15/RXD)
RP16: J2.6, J6.36 (GPIO16)
RP17: J4.6, J6.11 (GPIO17)
RP18: J2.4, J6.38 (GPIO20/MOSI1)
RP19: J4.4, J6.15 (GPIO22)
RP20: J4.3, J6.16 (GPIO23)
RP21: J4.1, J6.18 (GPIO24)
SPDIF_OUT: CS1.3 (ANODE), J4.11
V3: C1.1, CS1.2 (CATHODE), J6.1 (3V3), J6.17 (3V3)
VCC: J4.18, J5.3 (VCC), J5.29 (VCC), J6.2 (5V), J6.4 (5V), R1.1, R2.1, R3.1, R4.1, R5.1, R6.1, R7.1, R8.1, U19.20 (VCC)
~DACK1: J3.9, J5.17 (~DACK1)
~IOR: J4.13, J5.14 (~IOR)
~IOW: J4.14, J5.13 (~IOW)
~MEMR: J4.15, J5.12 (~SMEMR)
~MEMW: J4.16, J5.11 (~SMEMW)
